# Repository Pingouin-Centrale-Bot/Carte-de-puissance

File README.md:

# Carte de puissance pour le robot

## Cahier des charges
### Général
 - Connecter une batterie jusqu'à 6s avec un connecteur XT60
 - Génerer une tension 5v
 - Avoir un connecteur pour brancher un convertisseur de tension externe (qu'on appelera V')
 - Alimenter 3 autres cartes, en 3 tensions différentes (Vbatt, 5v, et V')
 - Avoir une sortie dédié à l'alimentation du Pi (sortie en Vbatt)
 - Avoir un bouton (ou entrée bouton) pour l'allumage du système (permet au système de s'éteindre complétement en cas de batterie faible)

### Sécurité du robot
 - Brancher le Bouton d'Arrêt d'Urgence (BAU)
 - Être capable de couper l'alimentation Vbatt et 5v allant vers les cartes annexes
 - Signaler l'état du BAU au Pi (à ROS)

### Protection de la batterie
 - Être capable de couper l'alimentation du Pi
 - Connaitre l'état d'alimentation du Pi (est-il allumé ?)
 - Être capable de couper l'alimentation générale
 - Diode de protection
 - Fusible

### Affichage/feedback
 - Afficher l'état de charge de la batterie (pourcentage sur afficheur 7 segment)
 - Avertissement sonore lorsque la batterie est à plat
 - LED RGB indiquant l'état du système intégré au bouton de mise en marche

### Possibilitées
 - Mesurer le courant sortant de la batterie

## Configuration du pi
Dans `/boot/firmware/config.txt` sur ubuntu :
```
#dtparam=i2c_arm=on
[all]
# So the pi shutdowns when gpio4 is pulled low
dtoverlay=gpio-shutdown,gpio_pin=3,active_low=1,gpio_pull=up
# So the pi 
dtoverlay=gpio-poweroff,gpiopin=4             
```

## Problèmes rencontrés
- [] Il faut mettre une résistance en parallèle des diodes pour le contrôle des mosfets.

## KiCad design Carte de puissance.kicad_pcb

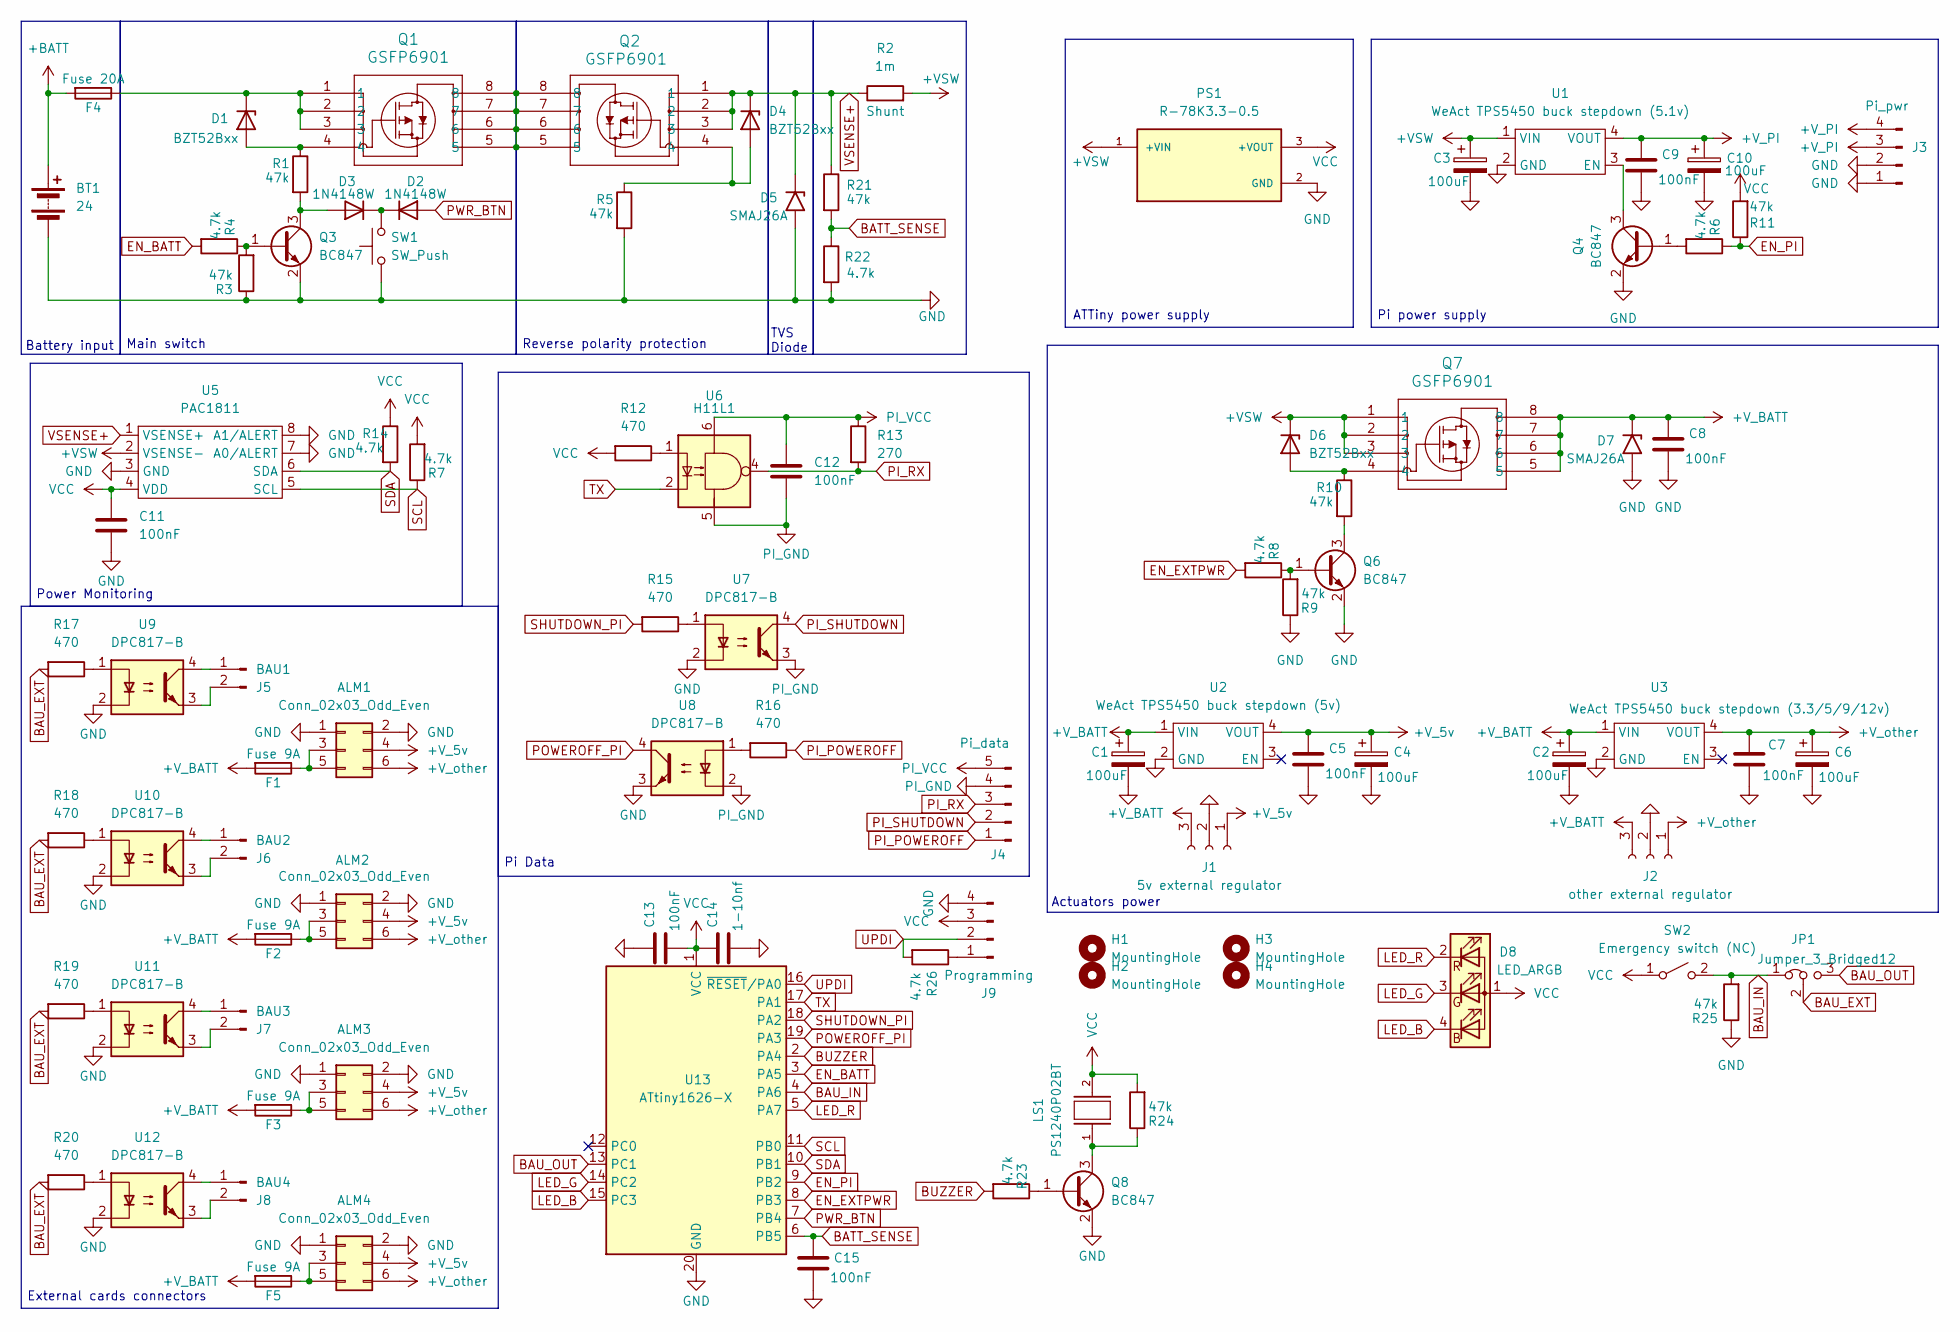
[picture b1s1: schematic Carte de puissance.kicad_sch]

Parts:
ALM1, ALM2, ALM3, ALM4: Conn_02x03_Odd_Even; Molex_Mini-Fit_Jr_5569-06A2_2x03_P4.20mm_Horizontal
BT1: 24; AMASS_XT60-M_1x02_P7.20mm_Vertical
C1, C2, C3, C4, C6, C10: 100uF; CP_Radial_D6.3mm_P2.50mm
C5, C7, C8, C9, C11, C12, C13, C15: 100nF; C_0805_2012Metric
C14: 1-10nf; C_0805_2012Metric
D1, D4, D6: BZT52Bxx; D_SOD-123F
D2, D3: 1N4148W; D_SOD-123
D5, D7: SMAJ26A; D_SMA
D8: LED_ARGB; JST_XH_B4B-XH-A_1x04_P2.50mm_Vertical
F1, F2, F3, F5: Fuse 9A; FUSE_3557_simple
F4: Fuse 20A; FUSE_3557_simple
H1, H2, H3, H4: MountingHole; MountingHole_3.2mm_M3
J1: 5v external regulator; MR30PB
J2: other external regulator; MR30PB
J3: Pi_pwr; JST_XH_B4B-XH-A_1x04_P2.50mm_Vertical
J4: Pi_data; JST_XH_B5B-XH-A_1x05_P2.50mm_Vertical
J5: BAU1; JST_XH_B2B-XH-A_1x02_P2.50mm_Vertical
J6: BAU2; JST_XH_B2B-XH-A_1x02_P2.50mm_Vertical
J7: BAU3; JST_XH_B2B-XH-A_1x02_P2.50mm_Vertical
J8: BAU4; JST_XH_B2B-XH-A_1x02_P2.50mm_Vertical
J9: Programming; PinHeader_1x04_P2.54mm_Vertical
JP1: Jumper_3_Bridged12; PinHeader_1x03_P2.54mm_Vertical
LS1: PS1240P02BT; XDCR_PS1240P02BT
PS1: R-78K3.3-0.5; CONV_R-78K3.3-0.5; PARTREV 0/2023
Q1, Q2, Q7: GSFP6901; PPAK5X6-8L_GAS
Q3, Q4, Q6, Q8: BC847; SOT-23
R1, R3, R5, R9, R10, R11, R21, R24, R25: 47k; R_0805_2012Metric
R2: 1m; R_2512_6332Metric
R4, R6, R7, R8, R14, R22, R23, R26: 4.7k; R_0805_2012Metric
R12, R15, R16, R17, R18, R19, R20: 470; R_0805_2012Metric
R13: 270; R_0805_2012Metric
SW1: SW_Push; JST_XH_B2B-XH-A_1x02_P2.50mm_Vertical
SW2: Emergency switch (NC); JST_XH_B2B-XH-A_1x02_P2.50mm_Vertical
U1: WeAct TPS5450 buck stepdown (5.1v); WeAct TPS5450 Buck Stepdown
U2: WeAct TPS5450 buck stepdown (5v); WeAct TPS5450 Buck Stepdown
U3: WeAct TPS5450 buck stepdown (3.3/5/9/12v); WeAct TPS5450 Buck Stepdown
U5: PAC1811
U6: H11L1; SMDIP-6_W9.53mm
U7, U8, U9, U10, U11, U12: DPC817-B; SMDIP-4_W11.48mm
U13: ATtiny1626-X; SSOP-20_5.3x7.2mm_P0.65mm

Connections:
+BATT: BT1.1 (+), F4.2
+VSW: C3.1, D6.1 (K), PS1.1 (+VIN), Q7.1, Q7.2, Q7.3, R2.2, U1.1 (VIN), U5.2 (VSENSE-)
+V_5v: ALM1.4, ALM2.4, ALM3.4, ALM4.4, C4.1, C5.1, J1.1, U2.4 (VOUT)
+V_BATT: C1.1, C2.1, C8.1, D7.1 (A1), F1.2, F2.2, F3.2, F5.2, J1.3, J2.3, Q7.5, Q7.6, Q7.7, Q7.8, U2.1 (VIN), U3.1 (VIN)
+V_PI: C9.1, C10.1, J3.3, J3.4, U1.4 (VOUT)
+V_other: ALM1.6, ALM2.6, ALM3.6, ALM4.6, C6.1, C7.1, J2.1, U3.4 (VOUT)
BATT_SENSE: C15.1, R21.2, R22.1, U13.6 (PB5)
BAU_EXT: JP1.2 (C), R17.2, R18.2, R19.2, R20.2
BAU_IN: JP1.1 (A), R25.2, SW2.2 (B), U13.4 (PA6)
BAU_OUT: JP1.3 (B), U13.13 (PC1)
BUZZER: R23.2, U13.2 (PA4)
EN_BATT: R4.2, U13.3 (PA5)
EN_EXTPWR: R8.2, U13.8 (PB3)
EN_PI: R6.1, R11.1, U13.9 (PB2)
GND: ALM1.1, ALM1.2, ALM2.1, ALM2.2, ALM3.1, ALM3.2, ALM4.1, ALM4.2, BT1.2 (-), C1.2, C2.2, C3.2, C4.2, C5.2, C6.2, C7.2, C8.2, C9.2, C10.2, C11.2, C13.1, C14.2, C15.2, D5.2 (A2), D7.2 (A2), J1.2, J2.2, J3.1, J3.2, J9.4, PS1.2 (GND), Q3.2 (E), Q4.2 (E), Q6.2 (E), Q8.2 (E), R3.1, R5.2, R9.1, R22.2, R25.1, SW1.1, U1.2 (GND), U2.2 (GND), U3.2 (GND), U5.3 (GND), U5.7 (A0/ALERT), U5.8 (A1/ALERT), U7.2, U8.3, U9.2, U10.2, U11.2, U12.2, U13.20 (GND)
LED_B: D8.4 (BK), U13.15 (PC3)
LED_G: D8.3 (GK), U13.14 (PC2)
LED_R: D8.2 (RK), U13.5 (PA7)
unnamed: ALM1.3, ALM1.5, F1.1
unnamed: ALM2.3, ALM2.5, F2.1
unnamed: ALM3.3, ALM3.5, F3.1
unnamed: ALM4.3, ALM4.5, F5.1
unnamed: D1.2 (A), Q1.4, R1.1
unnamed: D1.1 (K), F4.1, Q1.1, Q1.2, Q1.3
unnamed: D2.1 (K), D3.1 (K), SW1.2
unnamed: D3.2 (A), Q3.3 (C), R1.2
unnamed: D4.2 (A), Q2.4, R5.1
unnamed: D6.2 (A), Q7.4, R10.1
unnamed: J5.1, U9.4
unnamed: J5.2, U9.3
unnamed: J6.1, U10.4
unnamed: J6.2, U10.3
unnamed: J7.1, U11.4
unnamed: J7.2, U11.3
unnamed: J8.1, U12.4
unnamed: J8.2, U12.3
unnamed: J9.1, R26.1
unnamed: Q1.5, Q1.6, Q1.7, Q1.8, Q2.5, Q2.6, Q2.7, Q2.8
unnamed: Q3.1 (B), R3.2, R4.1
unnamed: Q4.1 (B), R6.2
unnamed: Q4.3 (C), U1.3 (EN)
unnamed: Q6.1 (B), R8.1, R9.2
unnamed: Q6.3 (C), R10.2
unnamed: Q8.1 (B), R23.1
unnamed: LS1.1, Q8.3 (C), R24.1
unnamed: R12.1, U6.1
unnamed: R15.1, U7.1
unnamed: R16.2, U8.1
unnamed: R17.1, U9.1
unnamed: R18.1, U10.1
unnamed: R19.1, U11.1
unnamed: R20.1, U12.1
PI_GND: C12.2, J4.4, U6.5, U7.3, U8.2
PI_POWEROFF: J4.1, R16.1
PI_RX: J4.3, R13.2, U6.4
PI_SHUTDOWN: J4.2, U7.4
PI_VCC: C12.1, J4.5, R13.1, U6.6
POWEROFF_PI: U8.4, U13.19 (PA3)
PWR_BTN: D2.2 (A), U13.7 (PB4)
SCL: R7.1, U5.5 (SCL), U13.11 (PB0)
SDA: R14.2, U5.6 (SDA), U13.10 (PB1)
SHUTDOWN_PI: R15.2, U13.18 (PA2)
TX: U6.2, U13.17 (PA1)
UPDI: J9.2, R26.2, U13.16 (~RESET/PA0)
VCC: C11.1, C13.2, C14.1, D8.1 (A), J9.3, LS1.2, PS1.3 (+VOUT), R7.2, R11.2, R12.2, R14.1, R24.2, SW2.1 (A), U5.4 (VDD), U13.1 (VCC)
VSENSE+: D4.1 (K), D5.1 (A1), Q2.1, Q2.2, Q2.3, R2.1, R21.1, U5.1 (VSENSE+)

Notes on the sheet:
Actuators power
ATTiny power supply
Pi Data
Pi power supply
External cards connectors
Power Monitoring
Main switch
TVS Diode
Battery input
Reverse polarity protection

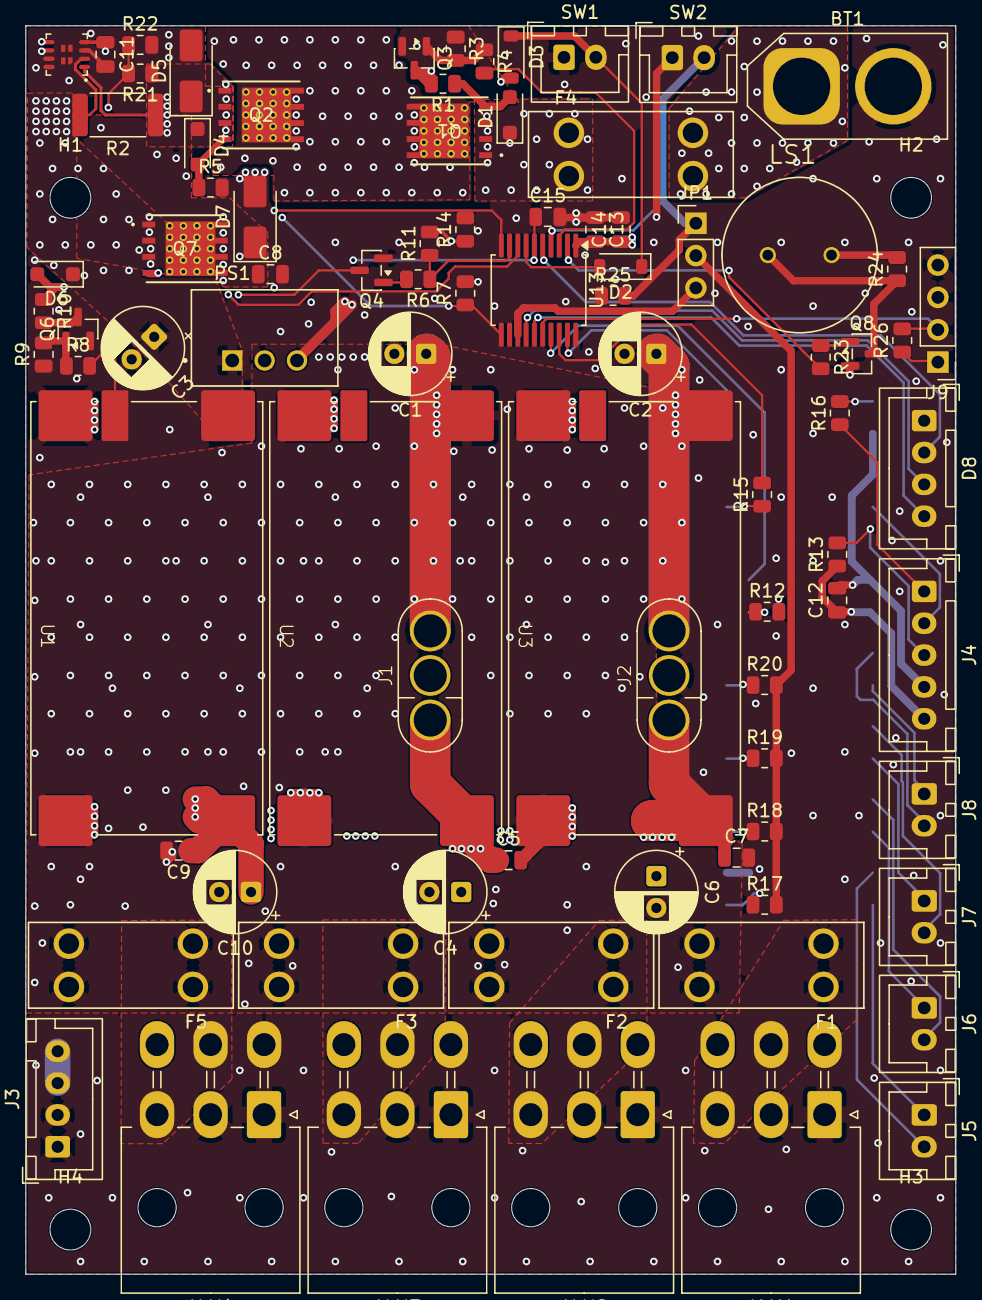
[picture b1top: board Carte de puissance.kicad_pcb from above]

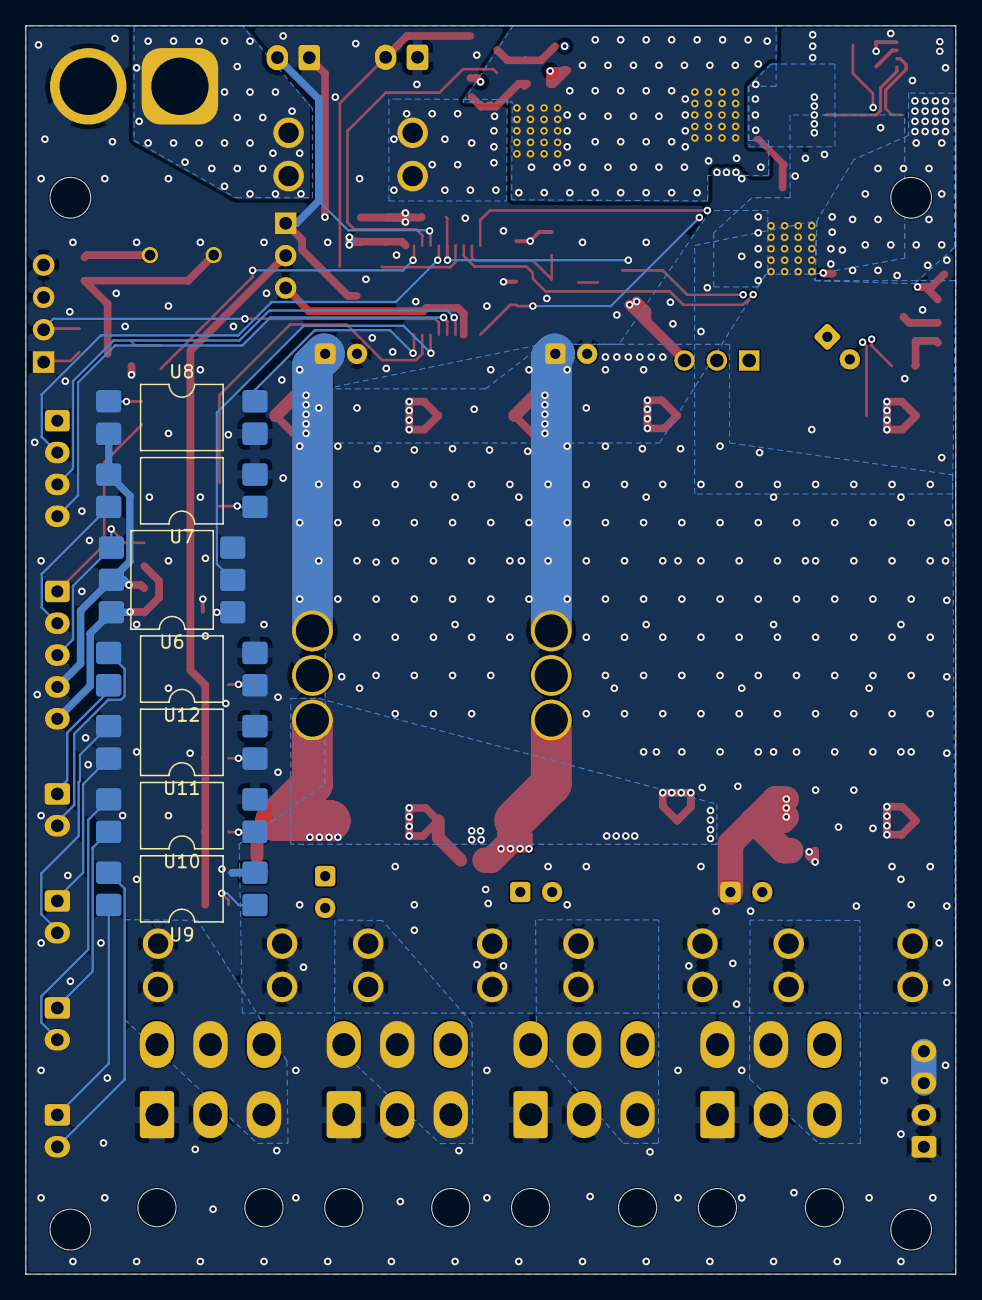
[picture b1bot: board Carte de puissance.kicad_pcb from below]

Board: 4 copper layers, 73.0 x 98.0 mm, 96 parts (7 on the bottom side), 66 nets.

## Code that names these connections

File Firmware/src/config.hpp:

#include <Arduino.h>

static const pin_size_t TX = PIN_PA1;
static const pin_size_t SHUTDOWN_PI = PIN_PA2; // To shutdown the Pi
static const pin_size_t POWEROFF_PI = PIN_PA3; // To tell if the Pi is shutdown
static const pin_size_t BUZZER = PIN_PA4;
static const pin_size_t EN_BATT = PIN_PA5;
static const pin_size_t BAU_IN = PIN_PA6;
static const pin_size_t LED_R = PIN_PA7;

// static const pin_size_t SCL = PIN_PB0; already exists
// static const pin_size_t SDA = PIN_PB1; already exists
static const pin_size_t EN_PI = PIN_PB2;
static const pin_size_t EN_EXTPWR = PIN_PB3;
static const pin_size_t PWR_BTN = PIN_PB4;
static const pin_size_t BATT_SENSE = PIN_PB5;

static const pin_size_t BAU_OUT = PIN_PC1;
static const pin_size_t LED_G = PIN_PC2;
static const pin_size_t LED_B = PIN_PC3;

static const float BATT_CORRECT = 24.18 / 24.00;
#ifdef ROBOT // 6s LiPo
static const int CELL_COUNT = 6;
static const uint16_t CRITICAL_HIGH_BATT = 1000 * 4.22 * CELL_COUNT; // Refuse to power on or power off if higher.
static const uint16_t HIGH_BATT = 1000 * 3.9 * CELL_COUNT;           // about 80% charge (green)
static const uint16_t NORMAL_BATT = 1000 * 3.75 * CELL_COUNT;        // about 40% charge (orange)
static const uint16_t MEDIUM_BATT = 1000 * 3.6 * CELL_COUNT;         // about 20% charge (red)
static const uint16_t LOW_BATT = 1000 * 3.5 * CELL_COUNT;            // about 10% charge (slow flashing red)
static const uint16_t VERY_LOW_BATT = 1000 * 3.4 * CELL_COUNT;       // about 5% charge (fast flashing red, force soft power off if lower)
static const uint16_t CRITICAL_LOW_BATT = 1000 * 3.1 * CELL_COUNT;   // If lower, refuse to power on or hard power off.
#endif
#ifdef NINJA // 4s LiFePo4
static const int CELL_COUNT = 4;
static const uint16_t CRITICAL_HIGH_BATT = 1000 * 3.65 * CELL_COUNT; // Refuse to power on or power off if higher.
static const uint16_t HIGH_BATT = 1000 * 3.32 * CELL_COUNT;          // about 80% charge (green)
static const uint16_t NORMAL_BATT = 1000 * 3.25 * CELL_COUNT;        // about 40% charge (orange)
static const uint16_t MEDIUM_BATT = 1000 * 3.2 * CELL_COUNT;         // about 20% charge (red)
static const uint16_t LOW_BATT = 1000 * 3.0 * CELL_COUNT;            // about 10% charge (slow flashing red)
static const uint16_t VERY_LOW_BATT = 1000 * 2.8 * CELL_COUNT;       // about 5% charge (fast flashing red, force soft power off if lower)
static const uint16_t CRITICAL_LOW_BATT = 1000 * 2.55 * CELL_COUNT;  // If lower, refuse to power on or hard power off.
#endif
#ifndef NINJA
#define NINJA false
#endif

enum Color : uint8_t
{
  Black = 0b000, // All off
  Red = 0b100,
  Green = 0b010,
  Blue = 0b001,
  Yellow = 0b110,  // Red + Green
  Magenta = 0b101, // Red + Blue
  Cyan = 0b011,    // Green + Blue
  White = 0b111    // All on
};

static const unsigned int LOW_NOTE = 1568;
static const unsigned int MEDIUM_NOTE = 1976;
static const unsigned int HIGH_NOTE = 2349;
static const unsigned int DEFAULT_NOTE = 2349;

static const Color LOW_COLOR = Cyan;
static const Color MEDIUM_COLOR = Magenta;
static const Color HIGH_COLOR = Yellow;

static const unsigned long batt_state_update_period = 200;  // ms
static const unsigned long pac1811_measure_period = 250;    // ms
static const unsigned long BAU_delay_before_powercut = 250; // ms

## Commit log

2026-03-24 Init
2026-04-07 Schematic fait
2026-04-07 Mise à jour de certains footprints
2026-04-07 Placement des composants
2026-04-07 Placement pour avoir une carte au format du module
2026-04-07 début de routage
2026-04-07 Changement des empreintes de fusible
2026-04-07 Ajout de l'empreinte des MR30PB
2026-04-11 Routage V2 partiel
2026-04-12 Routage V2 signaux fini Il reste encore la puissance à finir
2026-04-12 Routage fini reste à corriger les erreurs DRC, et à faire les graphiques
2026-04-13 Routing and debugging done, missing silkscreen
2026-04-13 Carte principale fini
2026-04-13 Correction du rectangle pour logo Aisler
2026-04-16 Ajout des modèles 3D manquants
2026-05-04 Code de firmware
2026-05-06 Correction of BAU startup routine
2026-05-14 Correction des dernières erreurs
